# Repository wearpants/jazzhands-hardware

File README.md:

# Jazz Hands PCBs

A small multi-PCB handheld keyboard for chording style input.

## Main

The main "brains" PCB, which accepts a nice!nano controller.
It exposes connection points with Molex Pico EZMate connectors for 5 `key` PCBs, and a 3-pin Molex Pico EZMate connector for use with the `power-reset` daughterboard PCB.
An untested IMU is also on the main PCB, for future use.

## Key

A small single key PCB with Molex Pico EZMate connector, Kailh hotswap socket, and mounting holes for possible assembly. One mounting hole "wing" is breakaway, as needed.

## Power/Reset

A small daughterboard PCB that contains a reset button and power switch, allowing those two components to be placed elsewhere in a case

# Firmware

See the `wearpants/jazzhands-zmk-config` repo for firmware for the main PCB with ZMK.

# Custom Modifications

It's possible to hack the current `main` PCB to also support a digital hall-effect sensor like the [DRV5023](https://www.ti.com/product/DRV5023) for use in a handheld "switchless design" using magnets only for activation in a glove.

# Production

All three PCBs can be produced by grabbing the generated files from the Actions tab and uploading to JLC, including partial assembly for the `main` PCB using JLC's PCBA service.

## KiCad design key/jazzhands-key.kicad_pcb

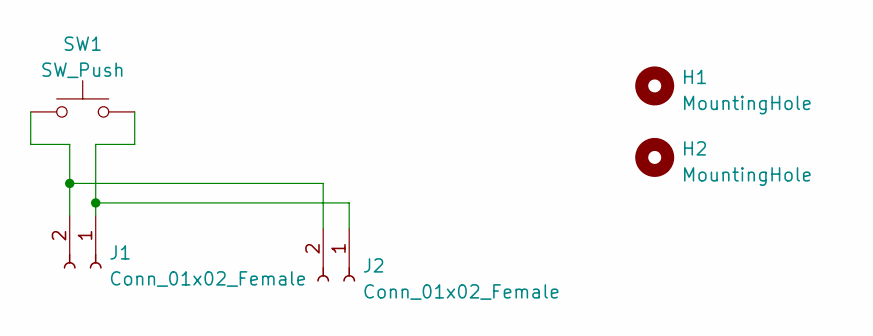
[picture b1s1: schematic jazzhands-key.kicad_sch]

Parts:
H1, H2: MountingHole; MountingHole_2.2mm_M2_Pad_TopBottom
J1, J2: Conn_01x02_Female; Molex_Pico-EZmate_78171-0002_1x02-1MP_P1.20mm_Vertical
SW1: SW_Push; MXOnly-1U-Hotswap-Antishear

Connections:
unnamed: J1.1, J2.1, SW1.2
unnamed: J1.2, J2.2, SW1.1

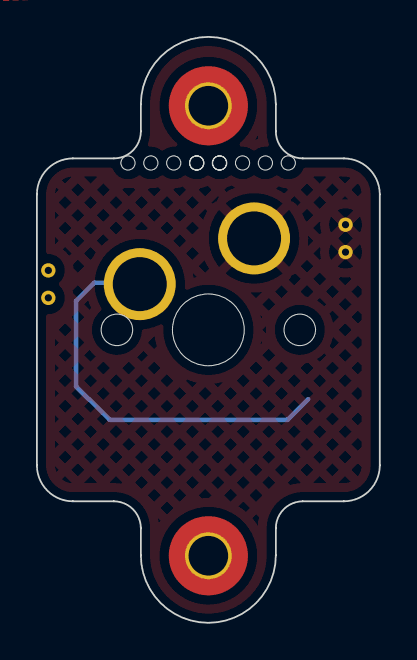
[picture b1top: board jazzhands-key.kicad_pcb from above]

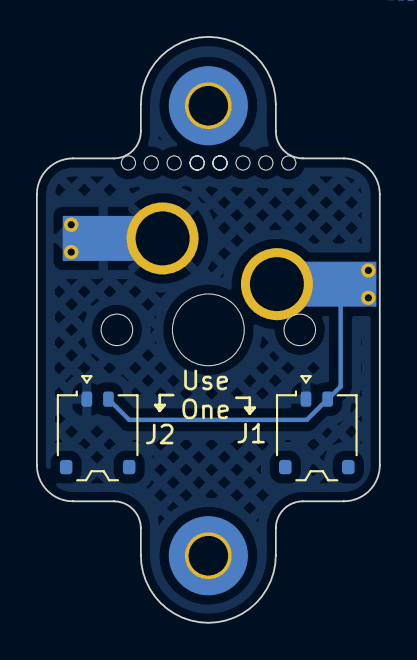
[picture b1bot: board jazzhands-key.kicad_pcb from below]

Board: 2 copper layers, 19.1 x 32.6 mm, 5 parts (2 on the bottom side), 2 nets.

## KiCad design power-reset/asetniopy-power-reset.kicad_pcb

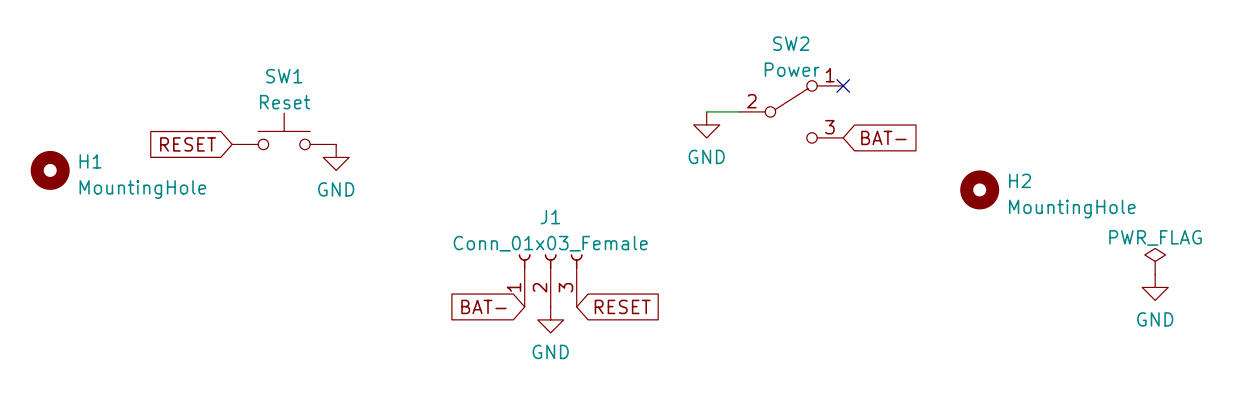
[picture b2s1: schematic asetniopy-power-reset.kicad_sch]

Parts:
H1, H2: MountingHole; MountingHole_3.2mm_M3_Pad
J1: Conn_01x03_Female; Molex_Pico-EZmate_78171-0003_1x03-1MP_P1.20mm_Vertical
SW1: Reset; Panasonic_EVQPUL_EVQPUC
SW2: Power; SW_SPDT_PCM12

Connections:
BAT-: J1.1, SW2.3 (C)
GND: J1.2, SW1.1, SW2.2 (B)
RESET: J1.3, SW1.2

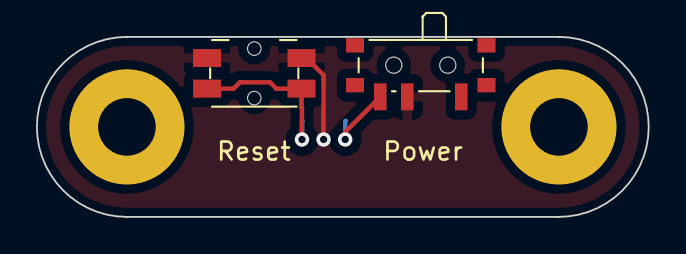
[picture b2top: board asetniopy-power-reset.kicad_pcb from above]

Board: 2 copper layers, 34.0 x 10.0 mm, 5 parts (1 on the bottom side), 3 nets.

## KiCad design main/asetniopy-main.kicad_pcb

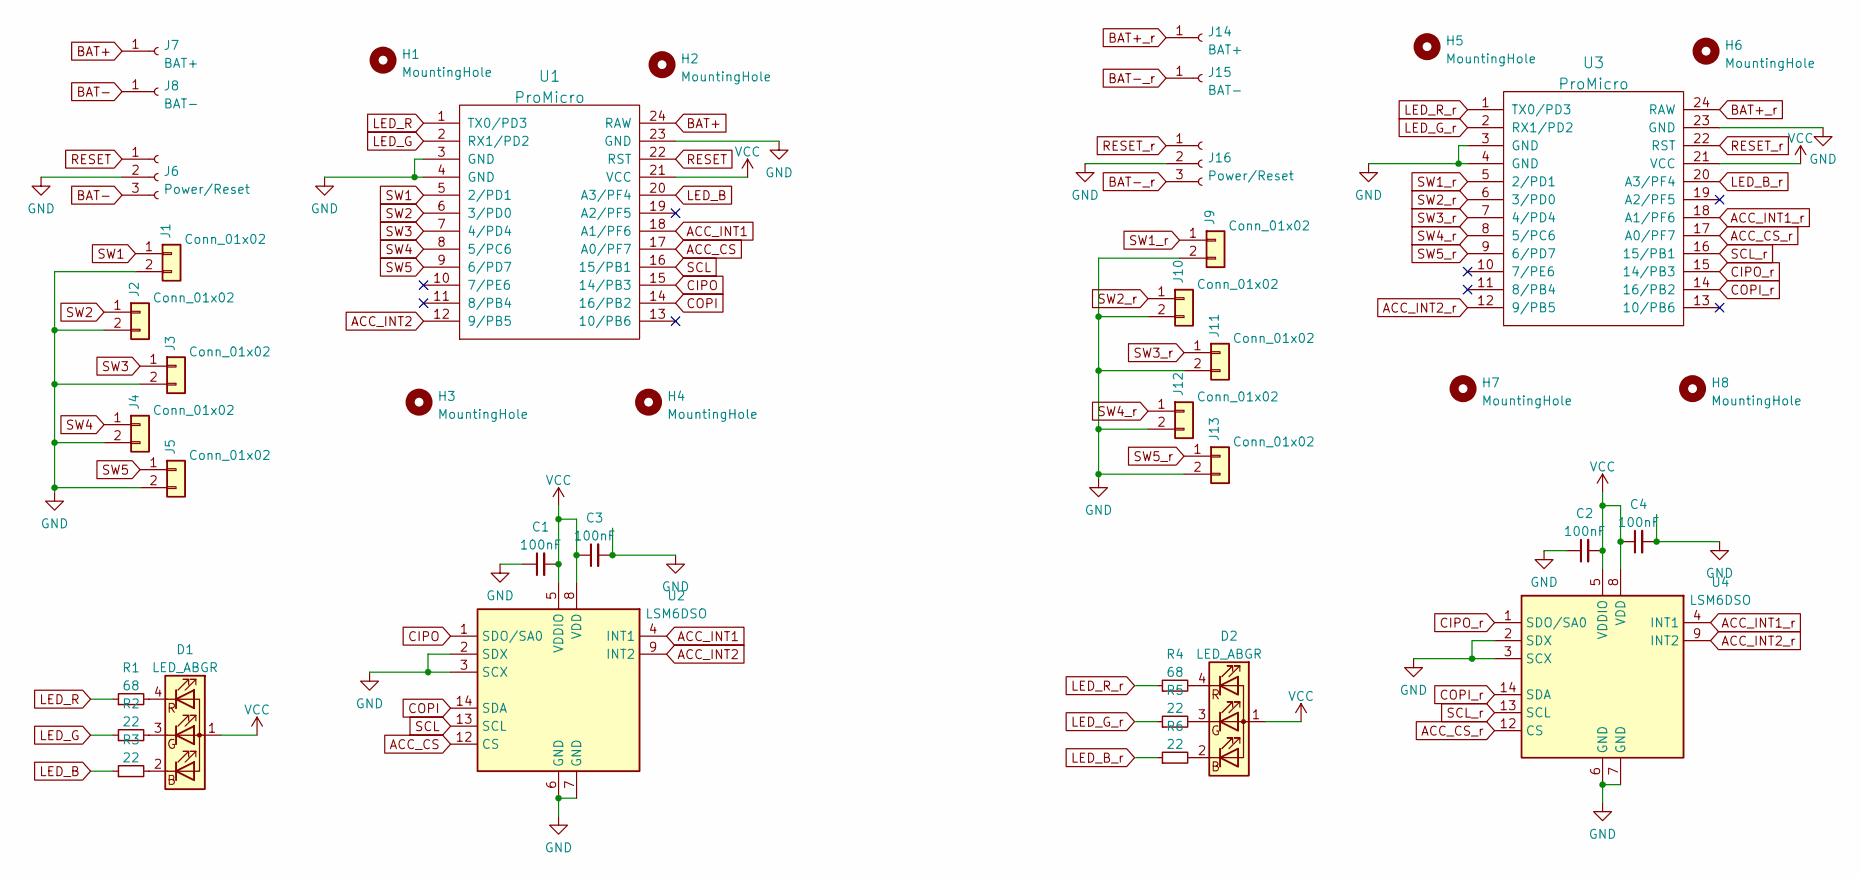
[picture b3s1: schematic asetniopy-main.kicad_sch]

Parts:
C1, C2, C3, C4: 100nF; C_0603_1608Metric; LCSC Part Number C14663
D1, D2: LED_ABGR; LED_RGB_Wuerth-PLCC4_3.2x2.8mm_150141M173100; LCSC Part Number C409779
H1, H2, H3, H4, H5, H6, H7, H8: MountingHole; MountingHole_2.2mm_M2_Pad
J1, J2, J3, J4, J5, J9, J10, J11, J12, J13: Conn_01x02; Molex_Pico-EZmate_78171-0002_1x02-1MP_P1.20mm_Vertical
J6, J16: Power/Reset; Molex_Pico-EZmate_78171-0003_1x03-1MP_P1.20mm_Vertical
J7, J14: BAT+; PinSocket_1x01_P2.54mm_Vertical
J8, J15: BAT-; PinSocket_1x01_P2.54mm_Vertical
R1, R4: 68; R_0603_1608Metric; LCSC Part Number C27592
R2, R3, R5, R6: 22; R_0603_1608Metric; LCSC Part Number C23345
U1, U3: ProMicro; ArduinoProMicro
U2, U4: LSM6DSO; PQFN50P250X300X86-14N; LCSC Part Number C2655100

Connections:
ACC_CS: U1.17 (A0/PF7), U2.12 (CS)
ACC_CS_r: U3.17 (A0/PF7), U4.12 (CS)
ACC_INT1: U1.18 (A1/PF6), U2.4 (INT1)
ACC_INT1_r: U3.18 (A1/PF6), U4.4 (INT1)
ACC_INT2: U1.12 (9/PB5), U2.9 (INT2)
ACC_INT2_r: U3.12 (9/PB5), U4.9 (INT2)
BAT+: J7.1, U1.24 (RAW)
BAT+_r: J14.1, U3.24 (RAW)
BAT-: J6.3, J8.1
BAT-_r: J15.1, J16.3
CIPO: U1.15 (14/PB3), U2.1 (SDO/SA0)
CIPO_r: U3.15 (14/PB3), U4.1 (SDO/SA0)
COPI: U1.14 (16/PB2), U2.14 (SDA)
COPI_r: U3.14 (16/PB2), U4.14 (SDA)
LED_B: R3.1, U1.20 (A3/PF4)
LED_B_r: R6.1, U3.20 (A3/PF4)
LED_G: R2.1, U1.2 (RX1/PD2)
LED_G_r: R5.1, U3.2 (RX1/PD2)
LED_R: R1.1, U1.1 (TX0/PD3)
LED_R_r: R4.1, U3.1 (TX0/PD3)
unnamed: D1.2 (BK), R3.2
unnamed: D1.3 (GK), R2.2
unnamed: D1.4 (RK), R1.2
unnamed: D2.2 (BK), R6.2
unnamed: D2.3 (GK), R5.2
unnamed: D2.4 (RK), R4.2
RESET: J6.1, U1.22 (RST)
RESET_r: J16.1, U3.22 (RST)
SCL: U1.16 (15/PB1), U2.13 (SCL)
SCL_r: U3.16 (15/PB1), U4.13 (SCL)
SW1: J1.1, U1.5 (2/PD1)
SW1_r: J9.1, U3.5 (2/PD1)
SW2: J2.1, U1.6 (3/PD0)
SW2_r: J10.1, U3.6 (3/PD0)
SW3: J3.1, U1.7 (4/PD4)
SW3_r: J11.1, U3.7 (4/PD4)
SW4: J4.1, U1.8 (5/PC6)
SW4_r: J12.1, U3.8 (5/PC6)
SW5: J5.1, U1.9 (6/PD7)
SW5_r: J13.1, U3.9 (6/PD7)

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
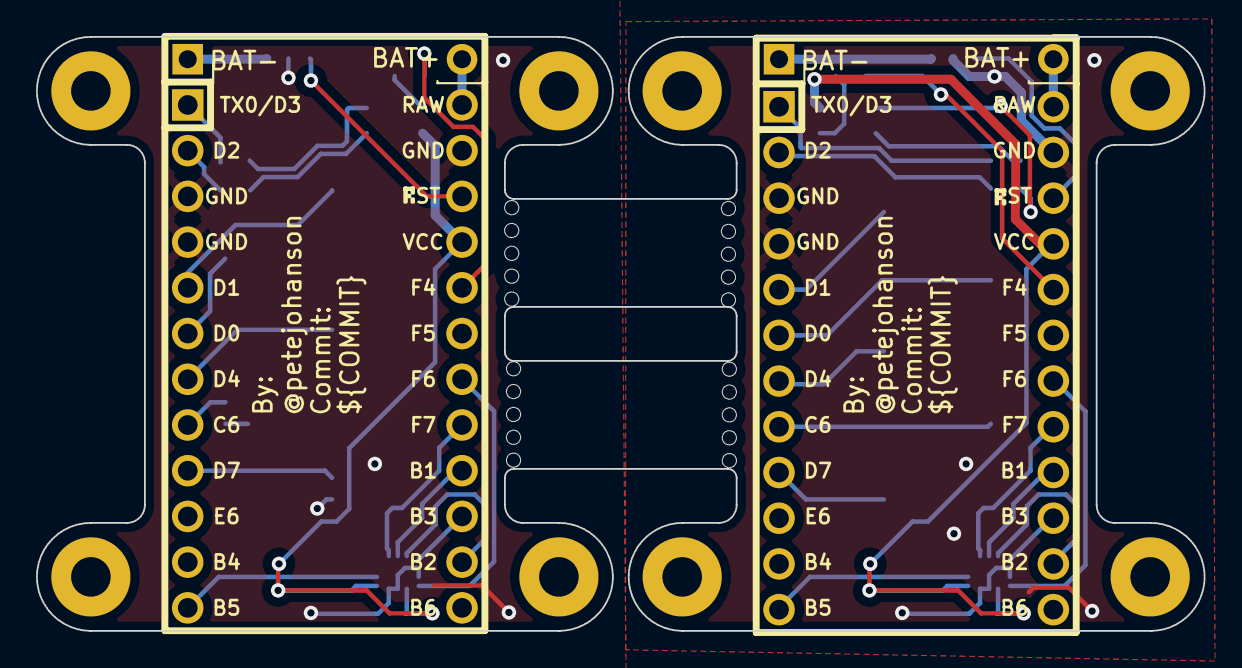
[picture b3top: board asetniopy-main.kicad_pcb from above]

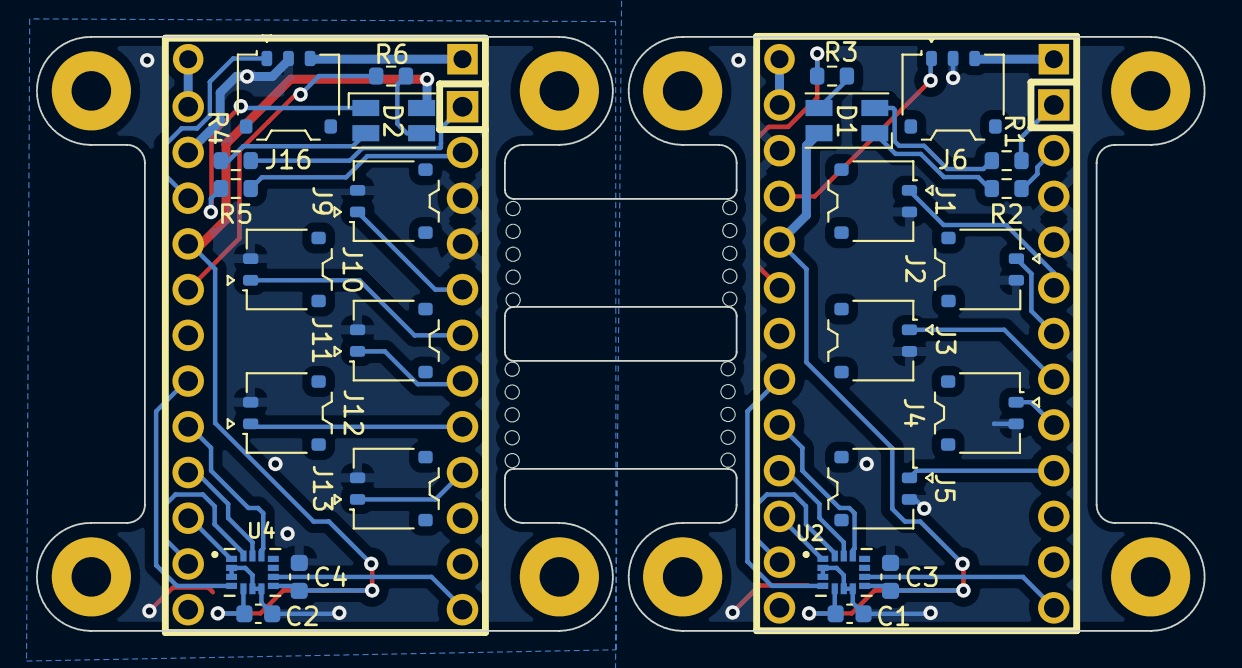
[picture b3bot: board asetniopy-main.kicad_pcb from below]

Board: 2 copper layers, 64.9 x 33.0 mm, 40 parts (26 on the bottom side), 44 nets.

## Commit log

2022-09-07 Initial individual key PCB.
    * Supports Kailh MX hotswap sockets
    * Molex Pico EZMate connector for direct wire connection.
    * Outline from constrained sketch in FreeCAD.
2022-09-25 Initial main daughterboard PCB.
2022-10-03 Initial power/reset PCB.
2022-10-03 Minor key PCB tweaks.
2022-10-06 Initial GH Actions workflow.
2022-10-06 Don't fail fast, add initial basic kibot files.
2022-10-06 Archive the JLCPCB zip files.
2022-10-06 Archive files, not zip.
2022-10-06 Assembly zip
2022-10-06 Add LCSC Part numbers for a few parts to test.
2022-10-06 More parts, rotation/placement fixes.
2022-10-06 Try rendering SVG and STEP files.
2022-10-06 Build a bit less verbosely.
2022-10-06 Archive renders.
2022-10-06 Ray tracing?
2022-10-06 Generate STEP file as well.
2022-10-06 Add missing 3d model.
2022-10-06 3D render bottom as well.
2022-10-06 Bump ray tracing wait time.
2022-10-06 Renders for the other boards.
2022-10-06 Timestamps
2022-10-06 Render top and bottom SVGs.
2022-10-06 Minor placement/silk tweaks.
2022-10-16 Switch to RGB LED.
2022-10-22 Move to LSM6DSO iNEMO IC.
2022-10-23 Left and right boards, joined via mouse bites.
2022-10-24 Add mouse bites for key mounting section
    * Move keeb.io lib up for re-use of the submodule.
    * Add second jumper to the key PCB.
2022-10-28 Bump action versions for Node 12 deprecation.
2022-10-28 Add part number for gyro.
2022-10-28 Proper 0603 resistors.
2022-10-28 A few silk label placement fixes.
2022-10-28 Fix assembly type for sensor.
2022-10-28 Fix sensor rotation for pick and place.
2022-10-31 Enlarge power/reset enough for JLC assembly.
2022-10-31 Add LSCS part numbers to power/reset.
2022-10-31 Fix property name typo.
2022-10-31 Fix reset button CPL rotation.
2023-02-23 Rename from asetniopy to jazzhands.
2023-02-23 Add a basic README.
2024-04-16 move pdfs
